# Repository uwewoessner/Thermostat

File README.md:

Control of Floor Heating based on an esp32 using MQTT

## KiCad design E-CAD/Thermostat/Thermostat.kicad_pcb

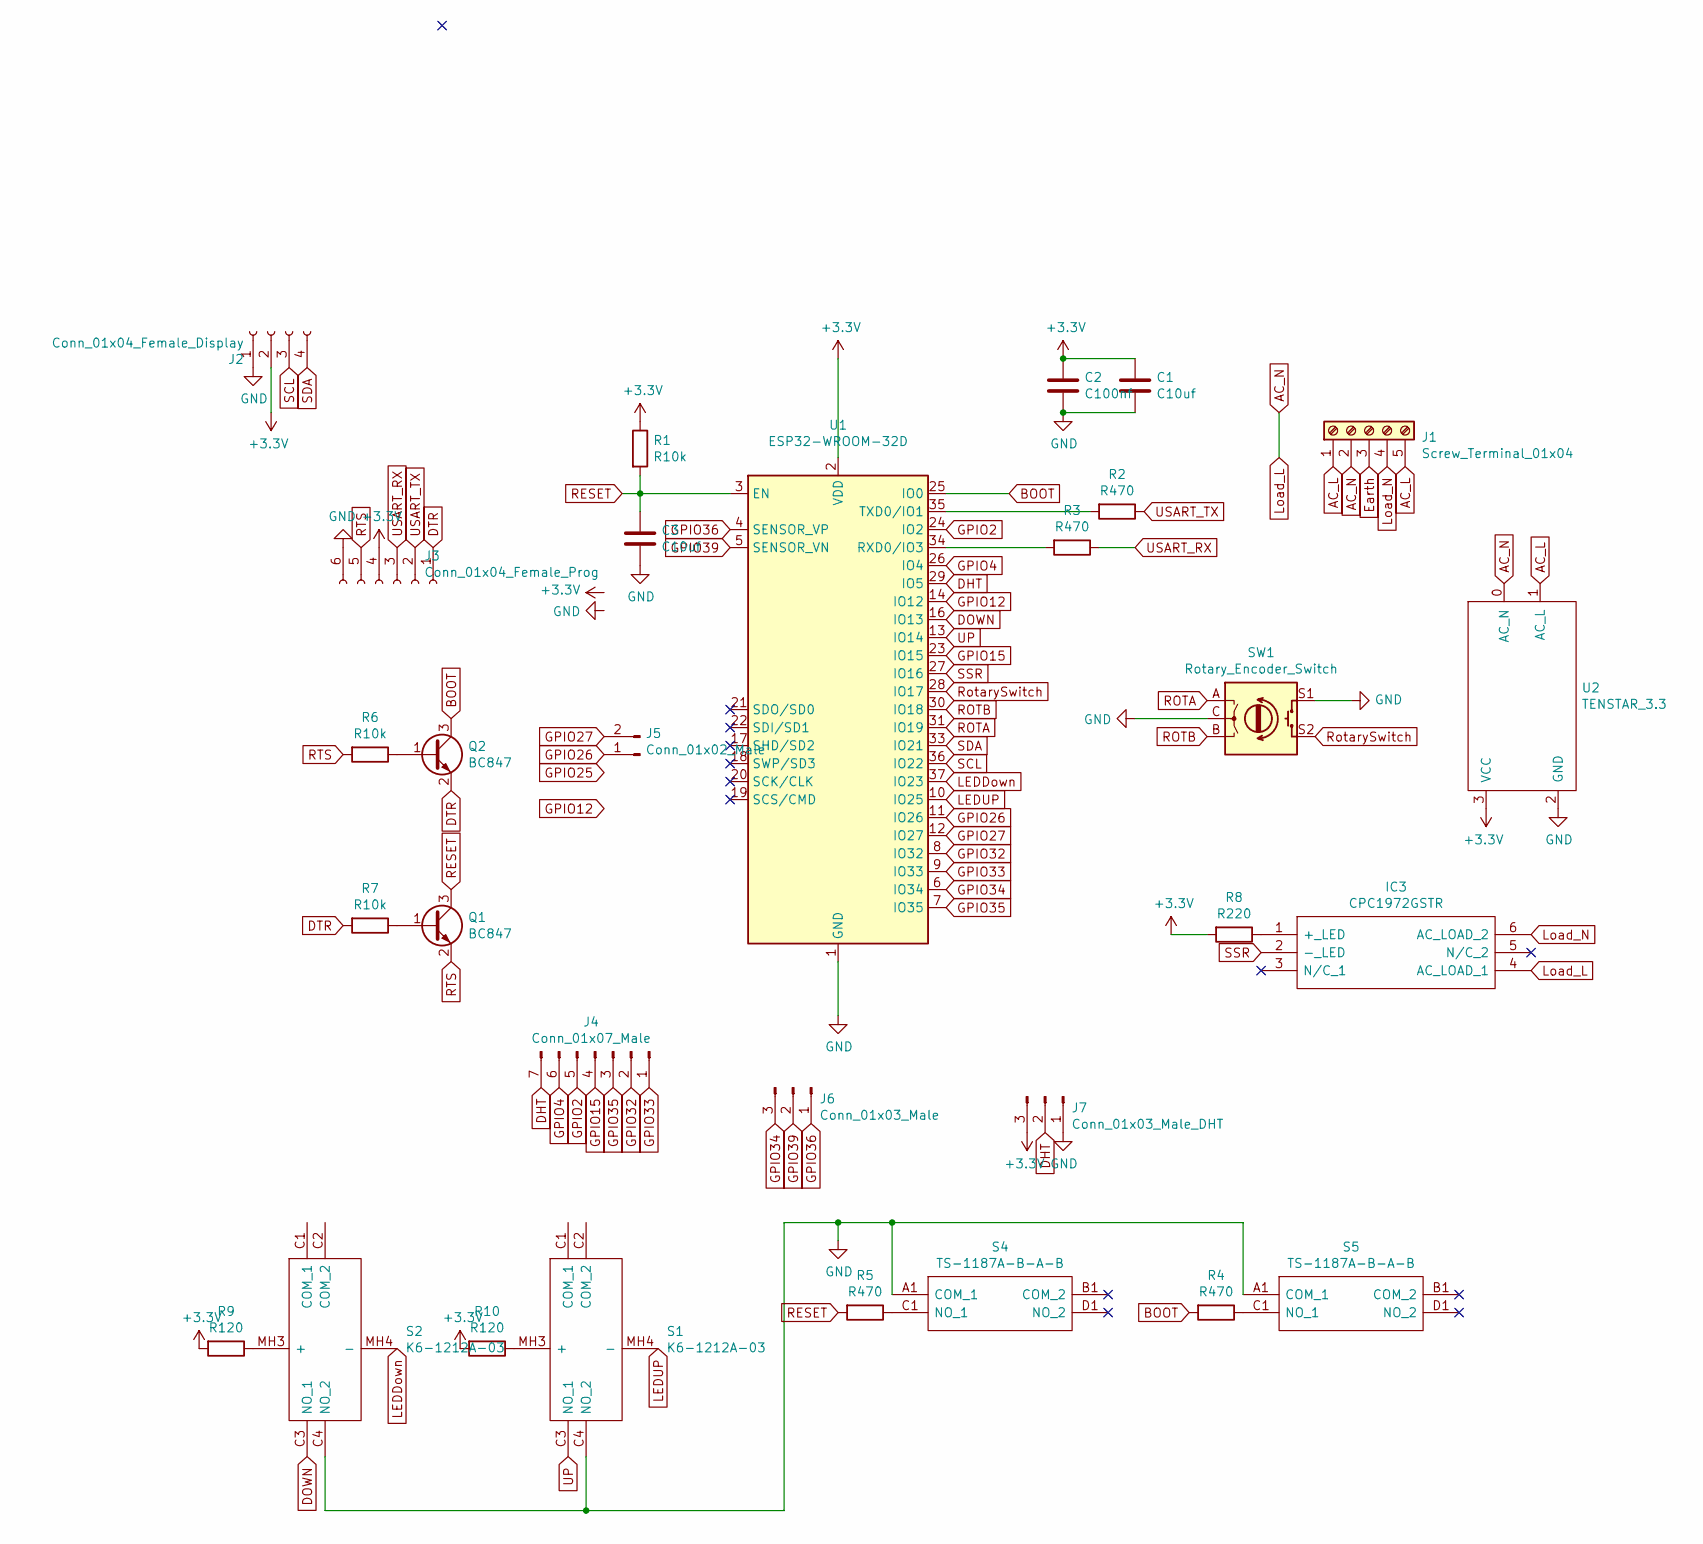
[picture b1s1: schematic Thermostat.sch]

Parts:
C1, C3: C10uf; C_1206_3216Metric; LCSC C13585
C2: C100nf; C_0805_2012Metric; LCSC C49678
IC3: CPC1972GSTR; SOP254P952X470-6N; Manufacturer_Part_Number CPC1972GSTR; Mouser Part Number 849-CPC1972GSTR
J1: Screw_Terminal_01x04; PhoenixContact_MCV_1,5_5-G-3.81_1x05_P3.81mm_Vertical
J2: Conn_01x04_Female_Display; PinHeader_1x04_P2.54mm_Vertical
J3: Conn_01x04_Female_Prog; PinSocket_1x06_P2.54mm_Vertical
J4: Conn_01x07_Male; PinHeader_1x07_P2.00mm_Vertical
J5: Conn_01x02_Male; PinHeader_1x02_P2.00mm_Vertical
J6: Conn_01x03_Male; PinHeader_1x03_P2.00mm_Vertical
J7: Conn_01x03_Male_DHT; PinHeader_1x03_P2.54mm_Vertical
Q1, Q2: BC847; SOT-23; LCSC C2146
R1, R6, R7: R10k; R_0805_2012Metric; LCSC C17414
R2, R3, R4, R5: R470; R_0805_2012Metric; LCSC C17710
R8: R220; R_0805_2012Metric; LCSC C17557
R9, R10: R120; R_0805_2012Metric; LCSC C17437
S1, S2: K6-1212A-03; K61212A03; Manufacturer_Part_Number K6-1212A-03
S4, S5: TS-1187A-B-A-B; TS1187ABAB; Manufacturer_Part_Number TS-1187A-B-A-B; LCSC C318884
SW1: Rotary_Encoder_Switch; RotaryEncoder_pec11r-4215k
U1: ESP32-WROOM-32D; ESP32-WROOM-32; LCSC C473012
U2: TENSTAR_3.3; TENSTAR_ROBOT_POWERSUPLY

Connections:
+3V3: C1.1, C2.1, J2.2, J3.4, J7.3, R1.1, R8.2, R9.2, R10.2, U1.2 (VDD), U2.3 (VCC)
AC_L: J1.1, J1.5, U2.1 (AC_L)
AC_N: IC3.4 (AC_LOAD_1), J1.2, U2.0 (AC_N)
BOOT: Q2.3 (C), R4.2, U1.25 (IO0)
DHT: J4.7, J7.2, U1.29 (IO5)
DOWN: S2.C3 (NO_1), U1.16 (IO13)
DTR: J3.1, Q2.2 (E), R7.2
Earth: J1.3
GND: C1.2, C2.2, C3.2, J2.1, J3.6, J7.1, S1.C4 (NO_2), S2.C4 (NO_2), S4.A1 (COM_1), S5.A1 (COM_1), SW1.C, SW1.S1, U1.1 (GND), U1.15 (GND), U1.38 (GND), U1.39 (GND), U2.2 (GND)
GPIO2: J4.5, U1.24 (IO2)
GPIO4: J4.6, U1.26 (IO4)
GPIO12: U1.14 (IO12)
GPIO15: J4.4, U1.23 (IO15)
GPIO26: J5.1, U1.11 (IO26)
GPIO27: J5.2, U1.12 (IO27)
GPIO32: J4.2, U1.8 (IO32)
GPIO33: J4.1, U1.9 (IO33)
GPIO34: J6.3, U1.6 (IO34)
GPIO35: J4.3, U1.7 (IO35)
GPIO36: J6.1, U1.4 (SENSOR_VP)
GPIO39: J6.2, U1.5 (SENSOR_VN)
LEDDown: S2.MH4 (-), U1.37 (IO23)
LEDUP: S1.MH4 (-), U1.10 (IO25)
Load_N: IC3.6 (AC_LOAD_2), J1.4
unnamed: IC3.1 (+_LED), R8.1
unnamed: Q1.1 (B), R7.1
unnamed: Q2.1 (B), R6.1
unnamed: R2.2, U1.35 (TXD0/IO1)
unnamed: R3.2, U1.34 (RXD0/IO3)
unnamed: R4.1, S5.C1 (NO_1)
unnamed: R5.1, S4.C1 (NO_1)
unnamed: R9.1, S2.MH3 (+)
unnamed: R10.1, S1.MH3 (+)
RESET: C3.1, Q1.3 (C), R1.2, R5.2, U1.3 (EN)
ROTA: SW1.A, U1.31 (IO19)
ROTB: SW1.B, U1.30 (IO18)
RTS: J3.5, Q1.2 (E), R6.2
RotarySwitch: SW1.S2, U1.28 (IO17)
SCL: J2.3, U1.36 (IO22)
SDA: J2.4, U1.33 (IO21)
SSR: IC3.2 (-_LED), U1.27 (IO16)
UP: S1.C3 (NO_1), U1.13 (IO14)
USART_RX: J3.3, R3.1
USART_TX: J3.2, R2.1

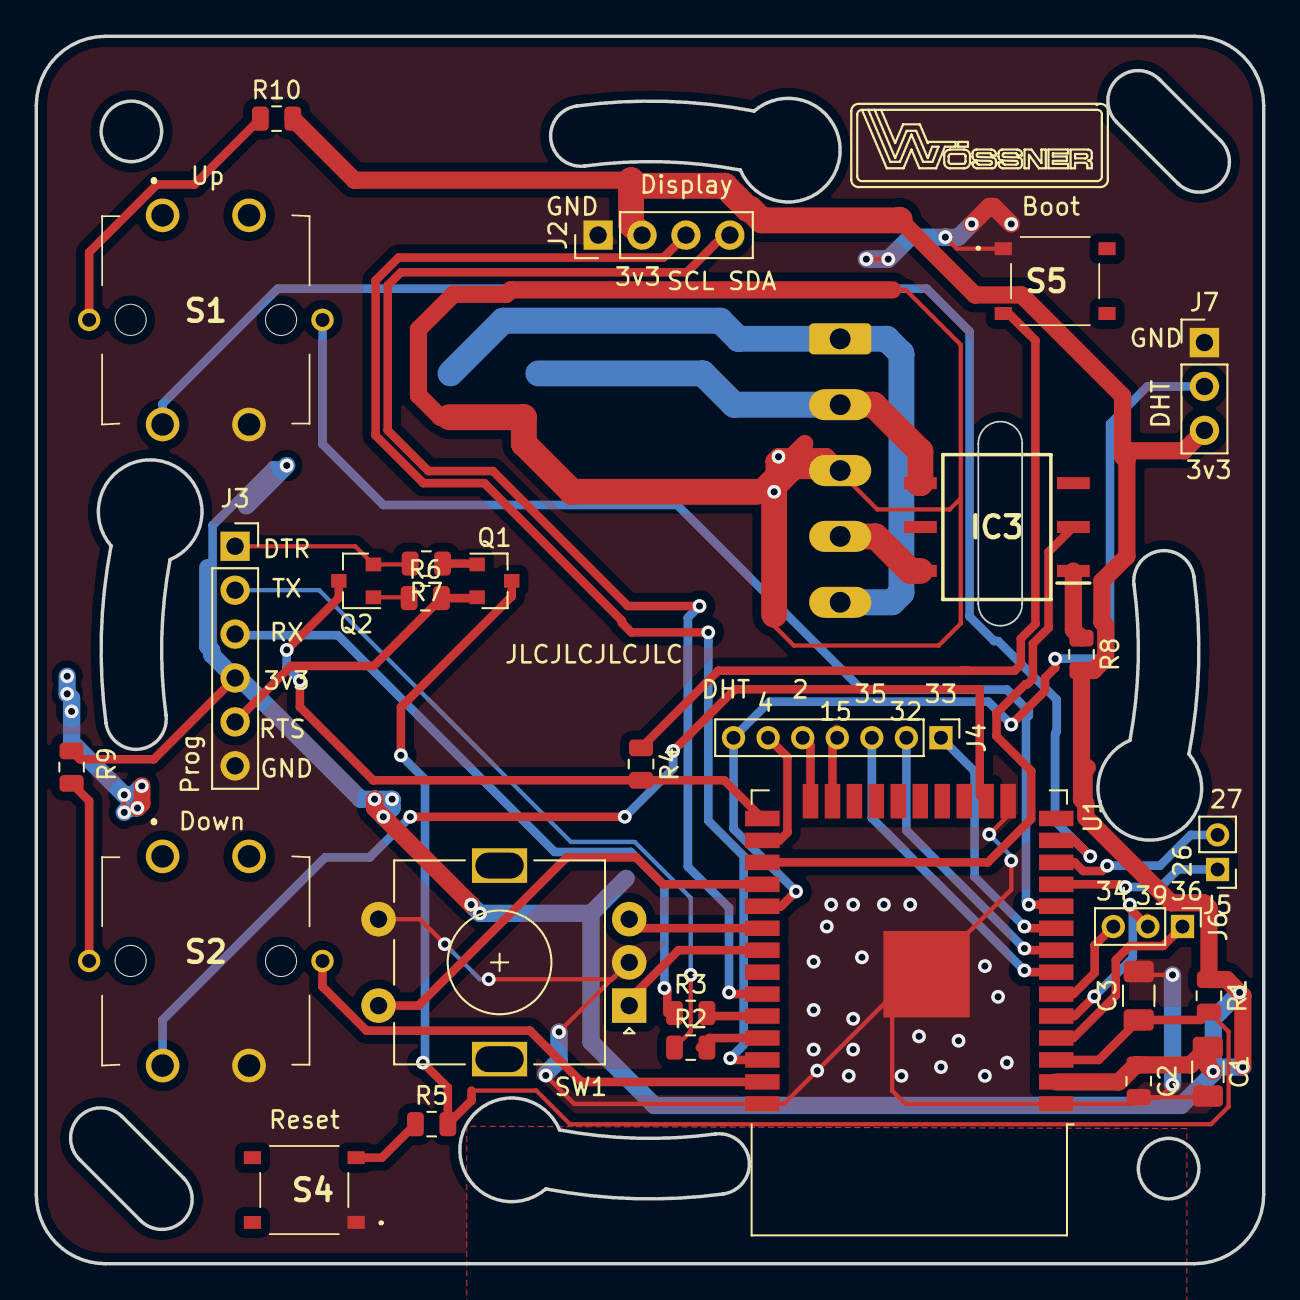
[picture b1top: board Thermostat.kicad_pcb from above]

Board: 2 copper layers, 71.0 x 71.0 mm, 29 parts (1 on the bottom side), 42 nets.

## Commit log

2022-12-07 initial version
2022-12-07 first version
2024-12-28 adjusting to api v3 and home assistant
2024-12-28 baks not needed
2025-02-01 Werkstatt und Büro
